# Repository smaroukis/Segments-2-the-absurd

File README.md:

For now, see <https://maroukis.net/sev-seg> 

> [!CAUTION] You will need to run a `git submodule init && git submodule update` to pull in changes to the TM1637 Seven Segment driver submodule code

## Building 
In the MCU directory i.e. `src/stm32` run `make flash`, see Makefile and VSCode `tasks.json` for details.

## Dependencies
- a forked version of nimaltd/tm1637 as a submodule in src/.../ThirdParty/tm1637 

Update the submodule _within the submodule directory_:
- `git fetch` && `git merge upstream/main`

# Revision History

## 2024-07-13 - Prototype (v-alpha) Hardware Finished
- __note kicad files and production gerbers are not in sync at this point__
- cleaned up git status in preparation for firmware development
- note at this point some edits were made to the kicad files that make it out of sync with the production file from commit #(TODO)
- moved prototype datasheets into a specific folder `.../2024-05-27-v-alpha`

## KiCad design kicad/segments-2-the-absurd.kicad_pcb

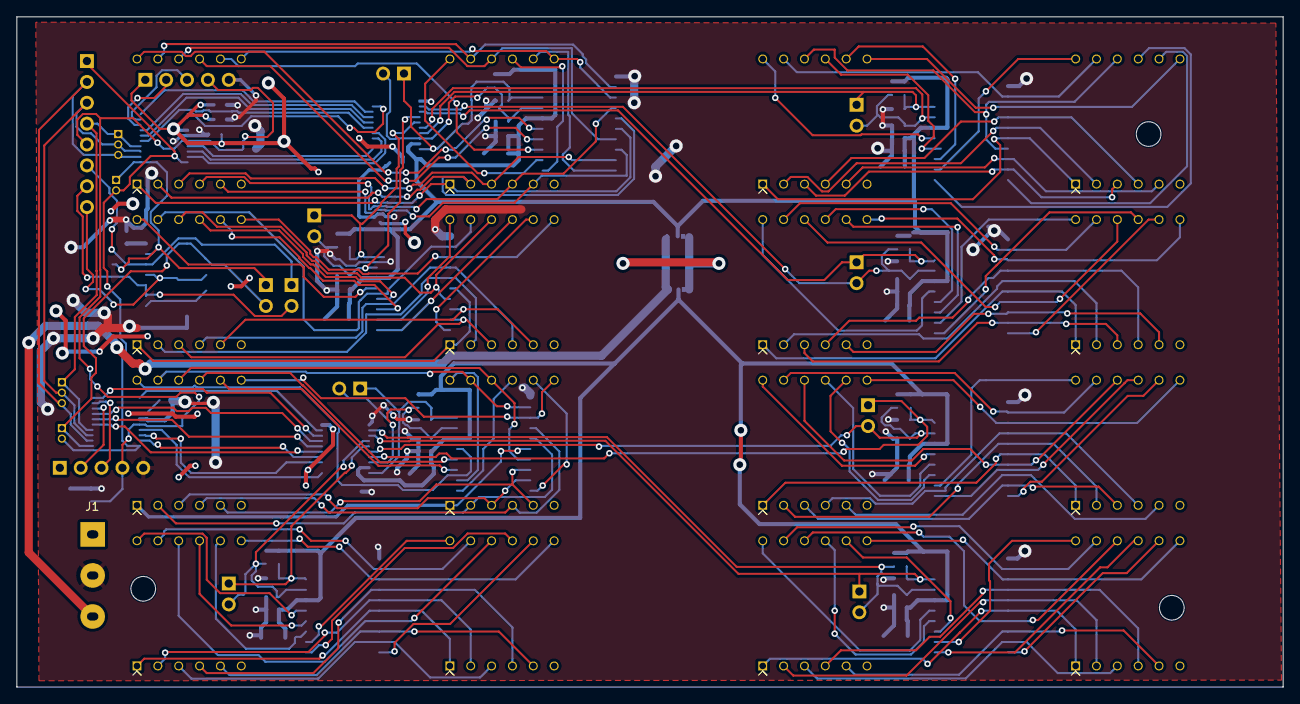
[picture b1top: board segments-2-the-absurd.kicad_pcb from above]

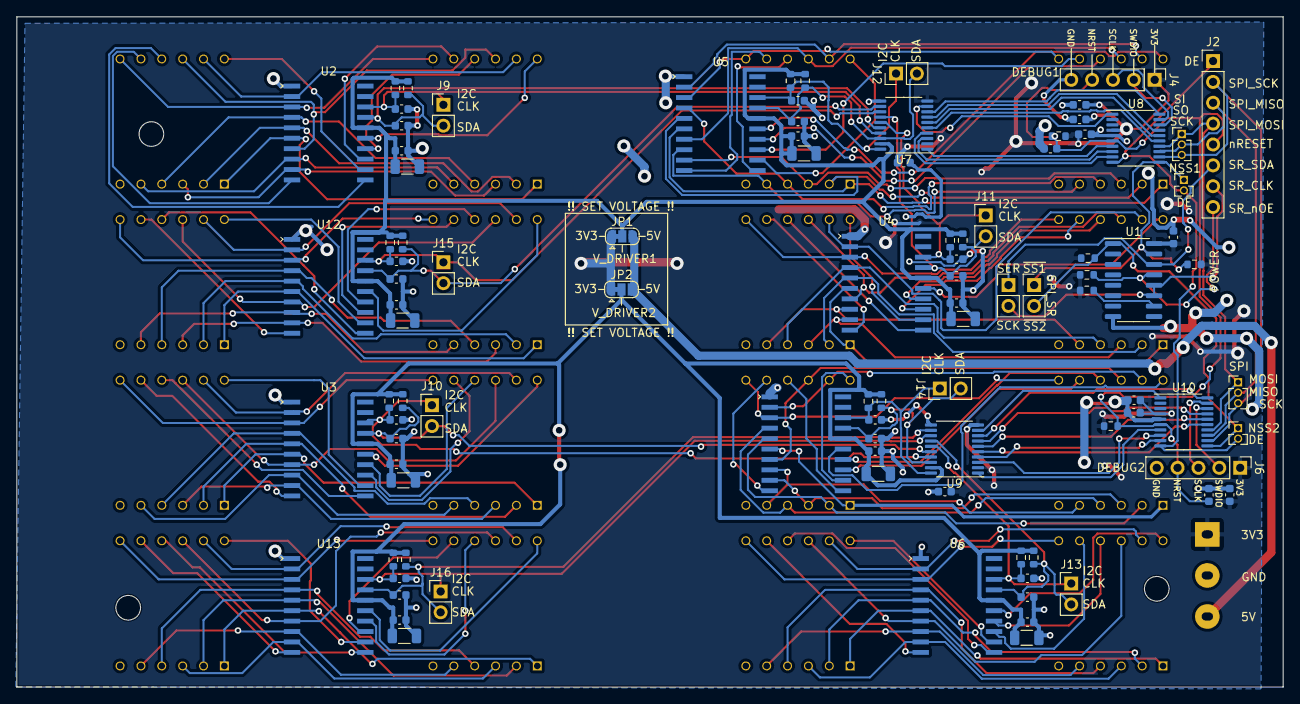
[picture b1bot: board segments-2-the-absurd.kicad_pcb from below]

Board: 2 copper layers, 154.2 x 81.6 mm, 114 parts (97 on the bottom side), 164 nets.

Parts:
C1, C5, C9, C13, C17, C21, C24, C26, C27, C28, C29, C31, C32, C33, C35, C39, C43: 100nF; C_0603_1608Metric
C4, C8, C12, C16, C20, C34, C38, C42: 100uF; C_1206_3216Metric
C6, C7, C10, C11, C14, C15, C18, C19, C22, C23, C36, C37, C40, C41, C44, C45: 100pF; C_0603_1608Metric
C25, C30: 4.7uF; C_0603_1608Metric
D1, D2, D3, D4, D5, D6, D7, D8, D9, D10, D11, D12, D13, D14, D15, D16: SP410561N; 7-Seg-3D_CA_ARKLED_SP410561N
J1: Conn_01x03_Pin; Power-Conn-3P-D0.65-P5-BD7.8x15
J2: Conn_01x08_Pin; PinHeader_1x08_P2.54mm_Vertical
J4, J6: Conn_01x05_Socket; PinHeader_1x05_P2.54mm_Vertical
J7, J8: Conn_01x02_Pin; PinHeader_1x02_P1.27mm_Vertical
J9, J10, J11, J12, J13, J14, J15, J16, J17, J20: Conn_01x02_Pin; PinHeader_1x02_P2.54mm_Vertical
J18, J19: Conn_01x03_Pin; PinHeader_1x03_P1.27mm_Vertical
JP1, JP2: Jumper_3_Bridged12; SolderJumper-3_P1.3mm_Bridged12_RoundedPad1.0x1.5mm
R1, R2, R3, R4, R5, R6, R7, R8, R9, R10, R11, R12, R13, R14, R15, R16, R17, R18, R19, R20, R21, R22: 10K; R_0603_1608Metric
U1: 74HC595; SOP-16_3.9x9.9mm_P1.27mm
U2, U3, U4, U5, U6, U11, U12, U13: TM1637; TM_TM1637(TA2007)_SOC-20_12.6x7.5_P1.27_PD0.44x2
U7, U9: TXS0108E; TSSOP-20_4.4x6.5mm_P0.65mm
U8, U10: STM32C011F6Px; TSSOP-20_4.4x6.5mm_P0.65mm

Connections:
+3V3: C1.2, C24.1, C25.1, C26.1, C28.2, C29.1, C30.1, C31.1, C33.2, J1.1, J4.1, J6.1, JP1.1 (A), JP2.1 (A), R1.1, R2.1, R3.1, R4.1, R15.1, R16.1, U1.16 (VCC), U7.2 (VCCA), U7.10 (OE), U8.4 (VDD), U9.2 (VCCA), U9.10 (OE), U10.4 (VDD)
+5V: J1.3, JP1.3 (B), JP2.3 (B)
/DISP_EN: J2.1, J7.2, J8.2, U8.10 (PA3), U10.10 (PA3)
/S2A_Serf1/A_CLK: C19.1, J12.1, R12.2, U5.18 (CLK), U7.20 (B1)
/S2A_Serf1/A_CLK': U7.1 (A1), U8.7 (PA0)
/S2A_Serf1/A_DAT: C18.1, J12.2, R11.2, U5.17 (DIO), U7.18 (B2)
/S2A_Serf1/A_DAT': U7.3 (A2), U8.8 (PA1)
/S2A_Serf1/B_CLK: C7.1, J9.1, R6.2, U2.18 (CLK), U7.17 (B3)
/S2A_Serf1/B_CLK': U7.4 (A3), U8.9 (PA2)
/S2A_Serf1/B_DAT: C6.1, J9.2, R5.2, U2.17 (DIO), U7.16 (B4)
/S2A_Serf1/B_DAT': U7.5 (A4), U8.15 (PA8)
/S2A_Serf1/C_CLK: C15.1, J11.1, R10.2, U4.18 (CLK), U7.15 (B5)
/S2A_Serf1/C_CLK': U7.6 (A5), U8.16 (PA9/PA11)
/S2A_Serf1/C_DAT: C14.1, J11.2, R9.2, U4.17 (DIO), U7.14 (B6)
/S2A_Serf1/C_DAT': U7.7 (A6), U8.17 (PA10/PA12)
/S2A_Serf1/D_CLK: C41.1, J15.1, R20.2, U7.13 (B7), U12.18 (CLK)
/S2A_Serf1/D_CLK': U7.8 (A7), U8.20 (PB6)
/S2A_Serf1/D_DAT: C40.1, J15.2, R19.2, U7.12 (B8), U12.17 (DIO)
/S2A_Serf1/D_DAT': U7.9 (A8), U8.1 (PB7)
/S2A_Serf1/SWCLK_BOOT0: J4.3, U8.19 (PA14)
/S2A_Serf1/SWDIO: J4.2, U8.18 (PA13)
/S2A_Serf1/V_DRIVER: C4.1, C5.1, C12.1, C13.1, C16.1, C17.1, C38.1, C39.1, JP1.2 (C), R5.1, R6.1, R9.1, R10.1, R11.1, R12.1, R19.1, R20.1, U2.16 (VDD), U4.16 (VDD), U5.16 (VDD), U7.19 (VCCB), U12.16 (VDD)
/S2A_Serf2/A_CLK: C37.1, J14.1, R18.2, U9.20 (B1), U11.18 (CLK)
/S2A_Serf2/A_CLK': U9.1 (A1), U10.7 (PA0)
/S2A_Serf2/A_DAT: C36.1, J14.2, R17.2, U9.18 (B2), U11.17 (DIO)
/S2A_Serf2/A_DAT': U9.3 (A2), U10.8 (PA1)
/S2A_Serf2/B_CLK: C11.1, J10.1, R8.2, U3.18 (CLK), U9.17 (B3)
/S2A_Serf2/B_CLK': U9.4 (A3), U10.9 (PA2)
/S2A_Serf2/B_DAT: C10.1, J10.2, R7.2, U3.17 (DIO), U9.16 (B4)
/S2A_Serf2/B_DAT': U9.5 (A4), U10.15 (PA8)
/S2A_Serf2/C_CLK: C23.1, J13.1, R14.2, U6.18 (CLK), U9.15 (B5)
/S2A_Serf2/C_CLK': U9.6 (A5), U10.16 (PA9/PA11)
/S2A_Serf2/C_DAT: C22.1, J13.2, R13.2, U6.17 (DIO), U9.14 (B6)
/S2A_Serf2/C_DAT': U9.7 (A6), U10.17 (PA10/PA12)
/S2A_Serf2/D_CLK: C45.1, J16.1, R22.2, U9.13 (B7), U13.18 (CLK)
/S2A_Serf2/D_CLK': U9.8 (A7), U10.20 (PB6)
/S2A_Serf2/D_DAT: C44.1, J16.2, R21.2, U9.12 (B8), U13.17 (DIO)
/S2A_Serf2/D_DAT': U9.9 (A8), U10.1 (PB7)
/S2A_Serf2/SWCLK_BOOT0: J6.3, U10.19 (PA14)
/S2A_Serf2/SWDIO: J6.2, U10.18 (PA13)
/S2A_Serf2/V_DRIVER: C8.1, C9.1, C20.1, C21.1, C34.1, C35.1, C42.1, C43.1, JP2.2 (C), R7.1, R8.1, R13.1, R14.1, R17.1, R18.1, R21.1, R22.1, U3.16 (VDD), U6.16 (VDD), U9.19 (VCCB), U11.16 (VDD), U13.16 (VDD)
/SPI_MISO: J2.3, J18.2, J19.2, U8.13 (PA6), U10.13 (PA6)
/SPI_MOSI: J2.4, J18.1, J19.1, U8.14 (PA7), U10.14 (PA7)
/SPI_NSS1: J7.1, J20.1, R1.2, U1.15 (QA), U8.11 (PA4)
/SPI_NSS2: J8.1, J20.2, R2.2, U1.1 (QB), U10.11 (PA4)
/SPI_SCK: J2.2, J18.3, J19.3, U8.12 (PA5), U10.12 (PA5)
/nRESET_ALL: C27.1, C32.1, J2.5, J4.4, J6.4, R15.2, R16.2, U8.6 (PF2), U10.6 (PF2)
/nSS_CLK: J2.7, J17.2, U1.11 (SRCLK), U1.12 (RCLK)
/nSS_SDA: J2.6, J17.1, U1.14 (SER)
/nSS_nOE: J2.8, R3.2, U1.13 (~OE)
GND: C1.1, C4.2, C5.2, C6.2, C7.2, C8.2, C9.2, C10.2, C11.2, C12.2, C13.2, C14.2, C15.2, C16.2, C17.2, C18.2, C19.2, C20.2, C21.2, C22.2, C23.2, C24.2, C25.2, C26.2, C27.2, C28.1, C29.2, C30.2, C31.2, C32.2, C33.1, C34.2, C35.2, C36.2, C37.2, C38.2, C39.2, C40.2, C41.2, C42.2, C43.2, C44.2, C45.2, J1.2, J4.5, J6.5, U1.8 (GND), U2.1 (GND), U3.1 (GND), U4.1 (GND), U5.1 (GND), U6.1 (GND), U7.11 (GND), U8.5 (VSS), U9.11 (GND), U10.5 (VSS), U11.1 (GND), U12.1 (GND), U13.1 (GND)
unnamed: D1.12 (DIG1), U5.15 (GRID1)
unnamed: D1.9 (DIG2), U5.14 (GRID2)
unnamed: D1.8 (DIG3), U5.13 (GRID3)
unnamed: D1.3 (DPX), D2.3 (DPX), U5.9 (SEG8/KS8)
unnamed: D1.11 (a), D2.11 (a), U5.2 (SEG1/KS1)
unnamed: D1.7 (b), D2.7 (b), U5.3 (SEG2/KS2)
unnamed: D1.4 (c), D2.4 (c), U5.4 (SEG3/KS3)
unnamed: D1.2 (d), D2.2 (d), U5.5 (SEG4/KS4)
unnamed: D1.1 (e), D2.1 (e), U5.6 (SEG5/KS5)
unnamed: D1.10 (f), D2.10 (f), U5.7 (SEG6/KS6)
unnamed: D1.5 (g), D2.5 (g), U5.8 (SEG7/KS7)
unnamed: D2.12 (DIG1), U5.12 (GRID4)
unnamed: D2.9 (DIG2), U5.11 (GRID5)
unnamed: D2.8 (DIG3), U5.10 (GRID6)
unnamed: D3.12 (DIG1), U2.15 (GRID1)
unnamed: D3.9 (DIG2), U2.14 (GRID2)
unnamed: D3.8 (DIG3), U2.13 (GRID3)
unnamed: D3.3 (DPX), D4.3 (DPX), U2.9 (SEG8/KS8)
unnamed: D3.11 (a), D4.11 (a), U2.2 (SEG1/KS1)
unnamed: D3.7 (b), D4.7 (b), U2.3 (SEG2/KS2)
unnamed: D3.4 (c), D4.4 (c), U2.4 (SEG3/KS3)
unnamed: D3.2 (d), D4.2 (d), U2.5 (SEG4/KS4)
unnamed: D3.1 (e), D4.1 (e), U2.6 (SEG5/KS5)
unnamed: D3.10 (f), D4.10 (f), U2.7 (SEG6/KS6)
unnamed: D3.5 (g), D4.5 (g), U2.8 (SEG7/KS7)
unnamed: D4.12 (DIG1), U2.12 (GRID4)
unnamed: D4.9 (DIG2), U2.11 (GRID5)
unnamed: D4.8 (DIG3), U2.10 (GRID6)
unnamed: D5.12 (DIG1), U4.15 (GRID1)
unnamed: D5.9 (DIG2), U4.14 (GRID2)
unnamed: D5.8 (DIG3), U4.13 (GRID3)
unnamed: D5.3 (DPX), D6.3 (DPX), U4.9 (SEG8/KS8)
unnamed: D5.11 (a), D6.11 (a), U4.2 (SEG1/KS1)
unnamed: D5.7 (b), D6.7 (b), U4.3 (SEG2/KS2)
unnamed: D5.4 (c), D6.4 (c), U4.4 (SEG3/KS3)
unnamed: D5.2 (d), D6.2 (d), U4.5 (SEG4/KS4)
unnamed: D5.1 (e), D6.1 (e), U4.6 (SEG5/KS5)
unnamed: D5.10 (f), D6.10 (f), U4.7 (SEG6/KS6)
unnamed: D5.5 (g), D6.5 (g), U4.8 (SEG7/KS7)
unnamed: D6.12 (DIG1), U4.12 (GRID4)
unnamed: D6.9 (DIG2), U4.11 (GRID5)
unnamed: D6.8 (DIG3), U4.10 (GRID6)
unnamed: D7.12 (DIG1), U12.15 (GRID1)
unnamed: D7.9 (DIG2), U12.14 (GRID2)
unnamed: D7.8 (DIG3), U12.13 (GRID3)
unnamed: D7.3 (DPX), D8.3 (DPX), U12.9 (SEG8/KS8)
unnamed: D7.11 (a), D8.11 (a), U12.2 (SEG1/KS1)
unnamed: D7.7 (b), D8.7 (b), U12.3 (SEG2/KS2)
unnamed: D7.4 (c), D8.4 (c), U12.4 (SEG3/KS3)
unnamed: D7.2 (d), D8.2 (d), U12.5 (SEG4/KS4)
unnamed: D7.1 (e), D8.1 (e), U12.6 (SEG5/KS5)
unnamed: D7.10 (f), D8.10 (f), U12.7 (SEG6/KS6)
unnamed: D7.5 (g), D8.5 (g), U12.8 (SEG7/KS7)
unnamed: D8.12 (DIG1), U12.12 (GRID4)
unnamed: D8.9 (DIG2), U12.11 (GRID5)
unnamed: D8.8 (DIG3), U12.10 (GRID6)
unnamed: D9.12 (DIG1), U11.15 (GRID1)
unnamed: D9.9 (DIG2), U11.14 (GRID2)
unnamed: D9.8 (DIG3), U11.13 (GRID3)
unnamed: D10.12 (DIG1), U11.12 (GRID4)
unnamed: D10.9 (DIG2), U11.11 (GRID5)
unnamed: D10.8 (DIG3), U11.10 (GRID6)
unnamed: D9.3 (DPX), D10.3 (DPX), U11.9 (SEG8/KS8)
unnamed: D9.11 (a), D10.11 (a), U11.2 (SEG1/KS1)
unnamed: D9.7 (b), D10.7 (b), U11.3 (SEG2/KS2)
unnamed: D9.4 (c), D10.4 (c), U11.4 (SEG3/KS3)
unnamed: D9.2 (d), D10.2 (d), U11.5 (SEG4/KS4)
unnamed: D9.1 (e), D10.1 (e), U11.6 (SEG5/KS5)
unnamed: D9.10 (f), D10.10 (f), U11.7 (SEG6/KS6)
unnamed: D9.5 (g), D10.5 (g), U11.8 (SEG7/KS7)
unnamed: D11.12 (DIG1), U3.15 (GRID1)
unnamed: D11.9 (DIG2), U3.14 (GRID2)
unnamed: D11.8 (DIG3), U3.13 (GRID3)
unnamed: D11.3 (DPX), D12.3 (DPX), U3.9 (SEG8/KS8)
unnamed: D11.11 (a), D12.11 (a), U3.2 (SEG1/KS1)
unnamed: D11.7 (b), D12.7 (b), U3.3 (SEG2/KS2)
unnamed: D11.4 (c), D12.4 (c), U3.4 (SEG3/KS3)
unnamed: D11.2 (d), D12.2 (d), U3.5 (SEG4/KS4)
unnamed: D11.1 (e), D12.1 (e), U3.6 (SEG5/KS5)
unnamed: D11.10 (f), D12.10 (f), U3.7 (SEG6/KS6)
unnamed: D11.5 (g), D12.5 (g), U3.8 (SEG7/KS7)
unnamed: D12.12 (DIG1), U3.12 (GRID4)
unnamed: D12.9 (DIG2), U3.11 (GRID5)
unnamed: D12.8 (DIG3), U3.10 (GRID6)
unnamed: D13.12 (DIG1), U6.15 (GRID1)
unnamed: D13.9 (DIG2), U6.14 (GRID2)
unnamed: D13.8 (DIG3), U6.13 (GRID3)
unnamed: D13.3 (DPX), D14.3 (DPX), U6.9 (SEG8/KS8)
unnamed: D13.11 (a), D14.11 (a), U6.2 (SEG1/KS1)
unnamed: D13.7 (b), D14.7 (b), U6.3 (SEG2/KS2)
unnamed: D13.4 (c), D14.4 (c), U6.4 (SEG3/KS3)
unnamed: D13.2 (d), D14.2 (d), U6.5 (SEG4/KS4)
unnamed: D13.1 (e), D14.1 (e), U6.6 (SEG5/KS5)
unnamed: D13.10 (f), D14.10 (f), U6.7 (SEG6/KS6)
unnamed: D13.5 (g), D14.5 (g), U6.8 (SEG7/KS7)
unnamed: D14.12 (DIG1), U6.12 (GRID4)
unnamed: D14.9 (DIG2), U6.11 (GRID5)
unnamed: D14.8 (DIG3), U6.10 (GRID6)
unnamed: D15.12 (DIG1), U13.15 (GRID1)
unnamed: D15.9 (DIG2), U13.14 (GRID2)
unnamed: D15.8 (DIG3), U13.13 (GRID3)
unnamed: D15.3 (DPX), D16.3 (DPX), U13.9 (SEG8/KS8)
unnamed: D15.11 (a), D16.11 (a), U13.2 (SEG1/KS1)
unnamed: D15.7 (b), D16.7 (b), U13.3 (SEG2/KS2)
unnamed: D15.4 (c), D16.4 (c), U13.4 (SEG3/KS3)
unnamed: D15.2 (d), D16.2 (d), U13.5 (SEG4/KS4)
unnamed: D15.1 (e), D16.1 (e), U13.6 (SEG5/KS5)
unnamed: D15.10 (f), D16.10 (f), U13.7 (SEG6/KS6)
unnamed: D15.5 (g), D16.5 (g), U13.8 (SEG7/KS7)
unnamed: D16.12 (DIG1), U13.12 (GRID4)
unnamed: D16.9 (DIG2), U13.11 (GRID5)
unnamed: D16.8 (DIG3), U13.10 (GRID6)
unnamed: R4.2, U1.10 (~SRCLR)

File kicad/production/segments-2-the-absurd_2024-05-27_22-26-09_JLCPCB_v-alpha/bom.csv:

Designator,Footprint,Quantity,Comment,LCSC Part #
"C1, C13, C17, C21, C24, C26, C27, C28, C29, C31, C32, C33, C35, C39, C43, C5, C9",603,17,100nF,C14663
"C10, C11, C14, C15, C18, C19, C22, C23, C36, C37, C40, C41, C44, C45, C6, C7",603,16,100pF,C14858
"C12, C16, C20, C34, C38, C4, C42, C8",1206,8,100uF,C15008
"C25, C30",603,2,4.7uF,C19666
"J10, J11, J12, J13, J14, J15, J16, J17, J20, J9",PinHeader_1x02_P2.54mm_Vertical,10,Conn_01x02_Pin,C492401
"J18, J19",PinHeader_1x03_P1.27mm_Vertical,2,Conn_01x03_Pin,DNP
J2,PinHeader_1x08_P2.54mm_Vertical,1,Conn_01x08_Pin,DNP
"J4, J6",PinHeader_1x05_P2.54mm_Vertical,2,Conn_01x05_Socket,DNP
"J7, J8",PinHeader_1x02_P1.27mm_Vertical,2,Conn_01x02_Pin,DNP
"JP1, JP2",SolderJumper-3_P1.3mm_Bridged12_RoundedPad1.0x1.5mm,2,Jumper_3_Bridged12,DNP
"R1, R10, R11, R12, R13, R14, R15, R16, R17, R18, R19, R2, R20, R21, R22, R3, R4, R5, R6, R7, R8, R9",603,22,10K,C25804
U1,SOP-16_3.9x9.9mm_P1.27mm,1,74HC595,C5451631
"U10, U8",TSSOP-20_4.4x6.5mm_P0.65mm,2,STM32C011F6Px,C5456198
"U11, U12, U13, U2, U3, U4, U5, U6",TM_TM1637(TA2007)_SOC-20_12.6x7.5_P1.27_PD0.44x2,8,TM1637,C5337160
"U7, U9",TSSOP-20_4.4x6.5mm_P0.65mm,2,TXS0108E,C17206

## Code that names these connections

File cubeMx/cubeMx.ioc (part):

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Mcu.Name=STM32C011F(4-6)Px
Mcu.Package=TSSOP20
Mcu.UserName=STM32C011F4Px
PA0.GPIOParameters=GPIO_Label
PA0.GPIO_Label=GPIO_A_CLK
PA0.Signal=GPIO_Output
PA1.GPIOParameters=GPIO_Label
PA1.GPIO_Label=GPIO_A_DAT
PA1.Signal=GPIO_Output
PA11\ [PA9].GPIOParameters=GPIO_Label
PA11\ [PA9].GPIO_Label=GPIO_C_CLK
PA11\ [PA9].Signal=GPIO_Output
PA12\ [PA10].GPIOParameters=GPIO_Label
PA12\ [PA10].GPIO_Label=GPIO_C_DAT
PA12\ [PA10].Signal=GPIO_Output
PA13.Mode=Serial_Wire
PA13.Signal=DEBUG_SWDIO
PA14-BOOT0.Mode=Serial_Wire
PA14-BOOT0.Signal=DEBUG_SWCLK
PA2.GPIOParameters=GPIO_Label
PA2.GPIO_Label=GPIO_B_CLK
PA2.Signal=GPIO_Output
PA3.Signal=GPIO_Output
PA4.Signal=SPI1_NSS
PA5.Signal=SPI1_SCK
PA6.Signal=SPI1_MISO
PA7.Signal=SPI1_MOSI
PA8.GPIOParameters=GPIO_Label
PA8.GPIO_Label=GPIO_B_DAT
PA8.Signal=GPIO_Output
RCC.HSE_VALUE=8000000
RCC.SYSCLKFreq_VALUE=12000000
board=custom

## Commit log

2024-04-23 init
2024-04-23 remove build artifacts
2024-04-23 added submodule
2024-04-23 readme edits for submodule
2024-04-24 tm1637 blinky
2024-04-24 janitor
2024-04-24 janitor 2
2024-04-27 testing displays and tm1637 lib - fading, scrolling
2024-05-13 commit 1
2024-07-13 adding v-alpha prototype gerbers (note out of sync with kicad files)
2024-07-13 added prototype datasheets
2024-07-13 tm1637 blinky on f303 nucleo
2024-07-15 testing for makefile changes
2024-07-15 mcu family variable placeholdings - working for f303, still TODO c011
